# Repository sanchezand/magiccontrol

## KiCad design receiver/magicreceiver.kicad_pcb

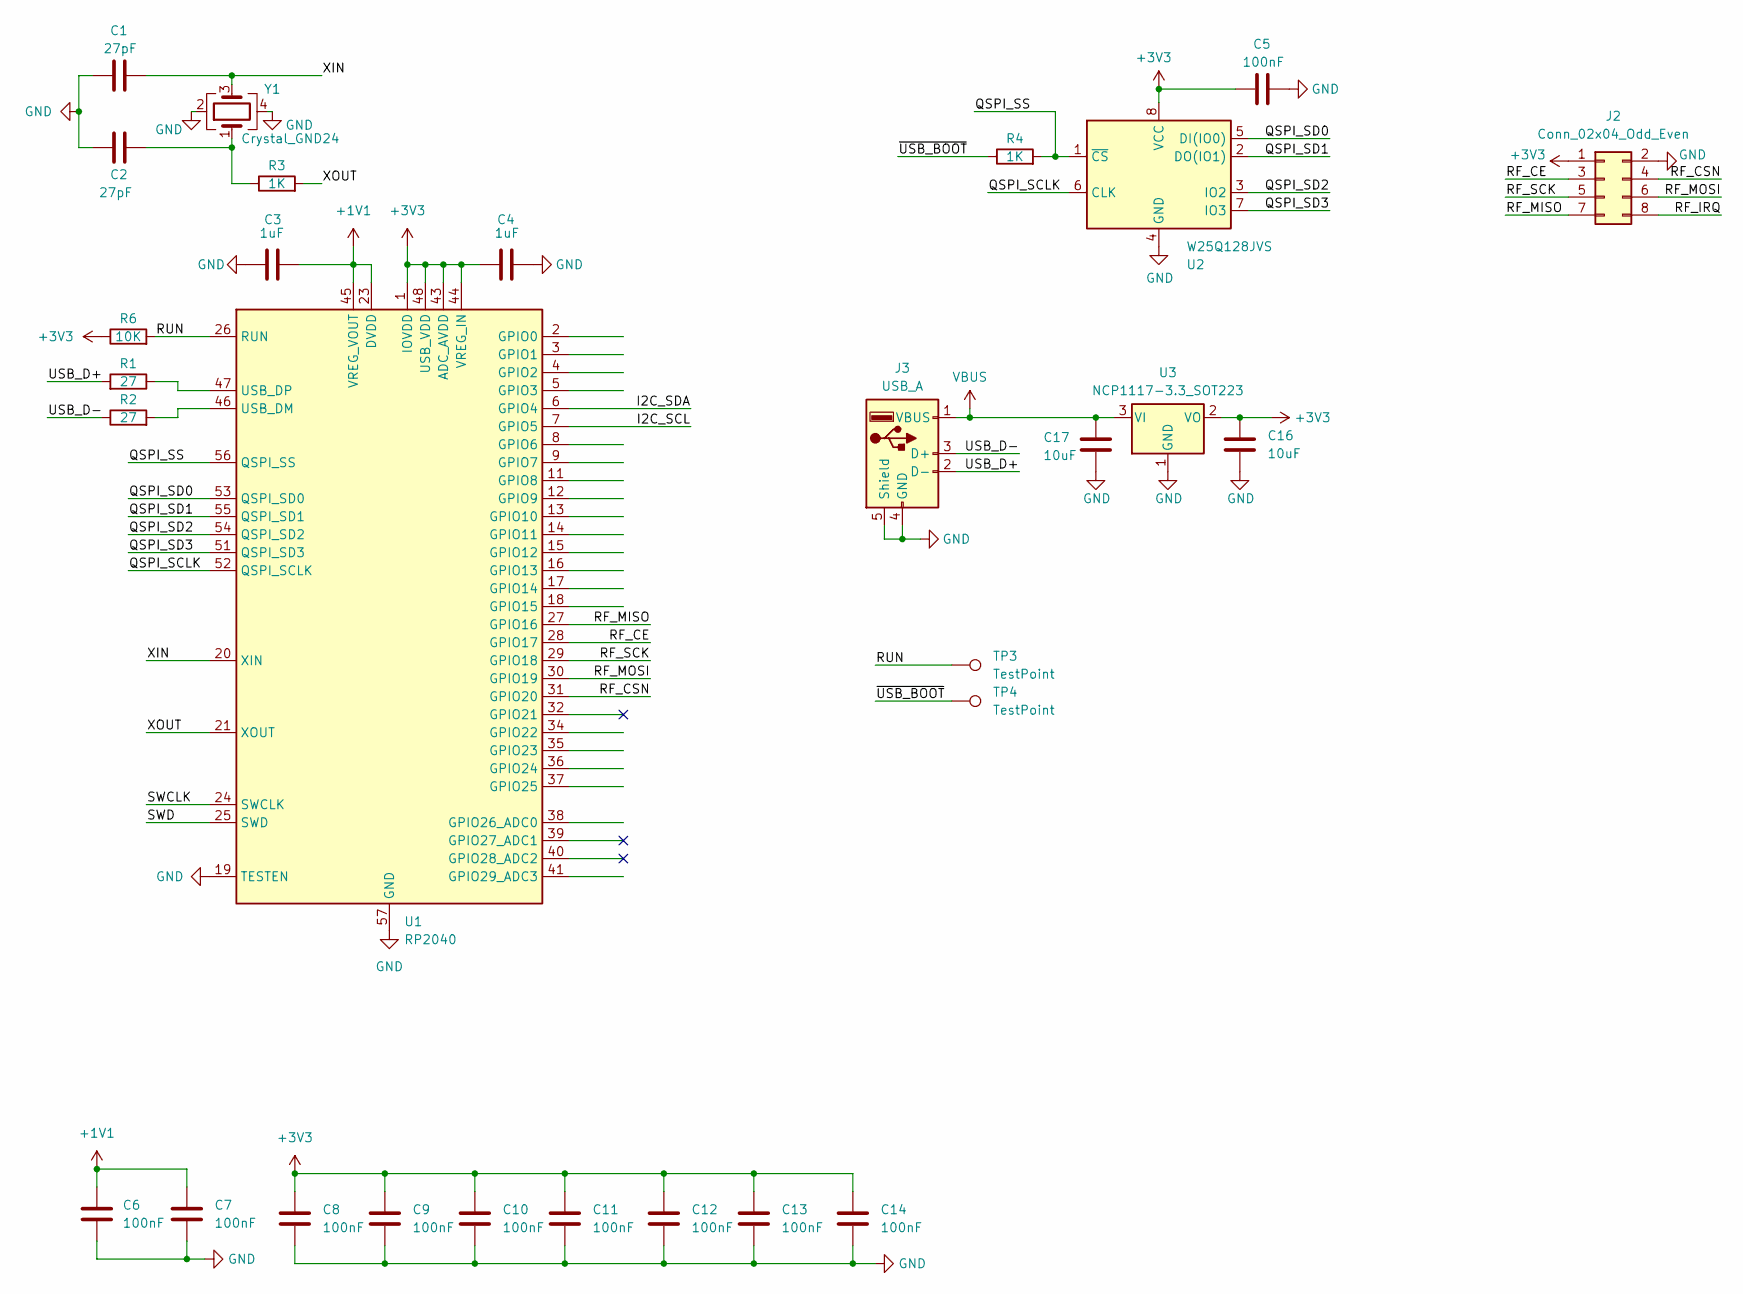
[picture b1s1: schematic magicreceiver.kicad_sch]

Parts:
C1, C2: 27pF; C_0603_1608Metric
C3, C4: 1uF; C_0603_1608Metric
C5, C6, C7, C8, C9, C10, C11, C12, C13, C14: 100nF; C_0603_1608Metric
C16, C17: 10uF; C_0603_1608Metric
J2: Conn_02x04_Odd_Even; NRF24L01-SMD
J3: USB_A; USB_EDGE
R1, R2: 27; R_0603_1608Metric
R3, R4: 1K; R_0603_1608Metric
R6: 10K; R_0603_1608Metric
TP3, TP4: TestPoint; TestPoint_Pad_D1.0mm
U1: RP2040; QFN-56-1EP_7x7mm_P0.4mm_EP3.2x3.2mm
U2: W25Q128JVS; SOIC-8_5.23x5.23mm_P1.27mm
U3: NCP1117-3.3_SOT223; SOT-223-3_TabPin2
Y1: Crystal_GND24; Crystal_SMD_3225-4Pin_3.2x2.5mm; LCSC C403945

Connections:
+1V1: C3.1, C6.2, C7.1, U1.23 (DVDD), U1.45 (VREG_VOUT), U1.50 (DVDD)
+3V3: C4.2, C5.1, C8.1, C9.1, C10.1, C11.1, C12.1, C13.1, C14.1, C16.1, J2.1, R6.1, U1.1 (IOVDD), U1.10 (IOVDD), U1.22 (IOVDD), U1.33 (IOVDD), U1.42 (IOVDD), U1.43 (ADC_AVDD), U1.44 (VREG_IN), U1.48 (USB_VDD), U1.49 (IOVDD), U2.8 (VCC), U3.2 (VO)
/I2C_SCL: U1.7 (GPIO5)
/I2C_SDA: U1.6 (GPIO4)
/QSPI_SCLK: U1.52 (QSPI_SCLK), U2.6 (CLK)
/QSPI_SD0: U1.53 (QSPI_SD0), U2.5 (DI(IO0))
/QSPI_SD1: U1.55 (QSPI_SD1), U2.2 (DO(IO1))
/QSPI_SD2: U1.54 (QSPI_SD2), U2.3 (IO2)
/QSPI_SD3: U1.51 (QSPI_SD3), U2.7 (IO3)
/QSPI_SS: R4.2, U1.56 (QSPI_SS), U2.1 (~CS)
/RF_CE: J2.3, U1.28 (GPIO17)
/RF_CSN: J2.4, U1.31 (GPIO20)
/RF_IRQ: J2.8
/RF_MISO: J2.7, U1.27 (GPIO16)
/RF_MOSI: J2.6, U1.30 (GPIO19)
/RF_SCK: J2.5, U1.29 (GPIO18)
/RUN: R6.2, TP3.1, U1.26 (RUN)
/SWCLK: U1.24 (SWCLK)
/SWD: U1.25 (SWD)
/USB_D+: J3.2 (D-), R1.2
/USB_D-: J3.3 (D+), R2.1
/XIN: C1.2, U1.20 (XIN), Y1.3
/XOUT: R3.2, U1.21 (XOUT)
/~USB_BOOT: R4.1, TP4.1
GND: C1.1, C2.1, C3.2, C4.1, C5.2, C6.1, C7.2, C8.2, C9.2, C10.2, C11.2, C12.2, C13.2, C14.2, C16.2, C17.2, J2.2, J3.4 (GND), J3.5 (Shield), U1.19 (TESTEN), U1.57 (GND), U2.4 (GND), U3.1 (GND), Y1.2, Y1.4
unnamed: C2.2, R3.1, Y1.1
unnamed: R2.2, U1.46 (USB_DM)
unnamed: R1.1, U1.47 (USB_DP)
VBUS: C17.1, J3.1 (VBUS), U3.3 (VI)

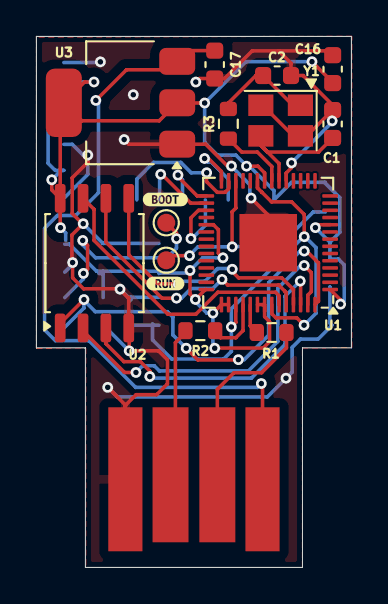
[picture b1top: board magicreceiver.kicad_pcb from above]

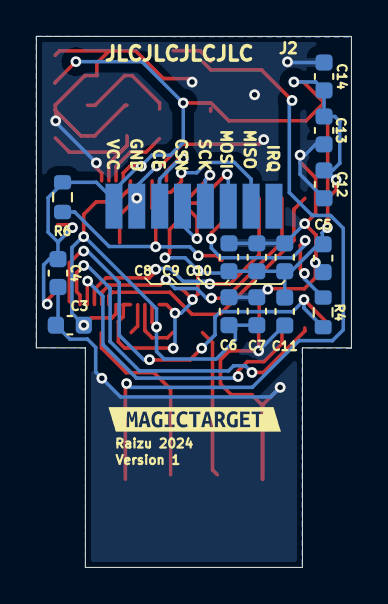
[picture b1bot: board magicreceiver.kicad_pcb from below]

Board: 2 copper layers, 17.5 x 29.5 mm, 32 parts (16 on the bottom side), 24 nets.

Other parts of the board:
kibuzzard-66566A5E: G***; kibuzzard-66566A5E
kibuzzard-66566A83: G***; kibuzzard-66566A83
kibuzzard-665666A1: G***; kibuzzard-665666A1
